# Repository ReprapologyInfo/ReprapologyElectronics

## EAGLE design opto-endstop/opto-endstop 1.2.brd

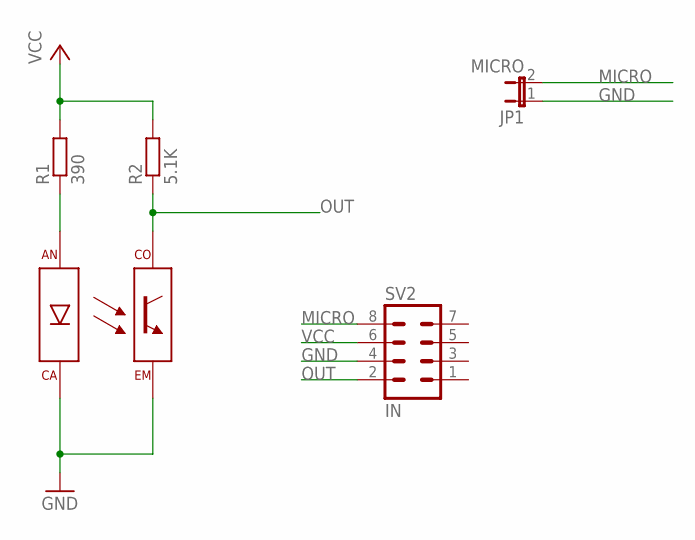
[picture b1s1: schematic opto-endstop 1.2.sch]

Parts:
JP1: MICRO; JP1
R1: 390; 0204/5
R2: 5.1K; 0204/5
SV2: IN; MA04-2
U$1: KTIR0521DS

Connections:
GND: JP1.1, SV2.4, U$1.CA, U$1.EM
MICRO: JP1.2, SV2.8
unnamed: R1.1, U$1.AN
OUT: R2.1, SV2.2, U$1.CO
VCC: R1.2, R2.2, SV2.6

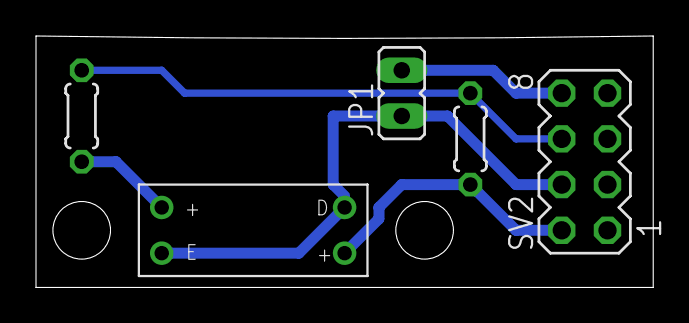
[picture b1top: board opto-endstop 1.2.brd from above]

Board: 2 copper layers, 34.3 x 14.0 mm, 5 parts (0 on the bottom side), 5 nets.

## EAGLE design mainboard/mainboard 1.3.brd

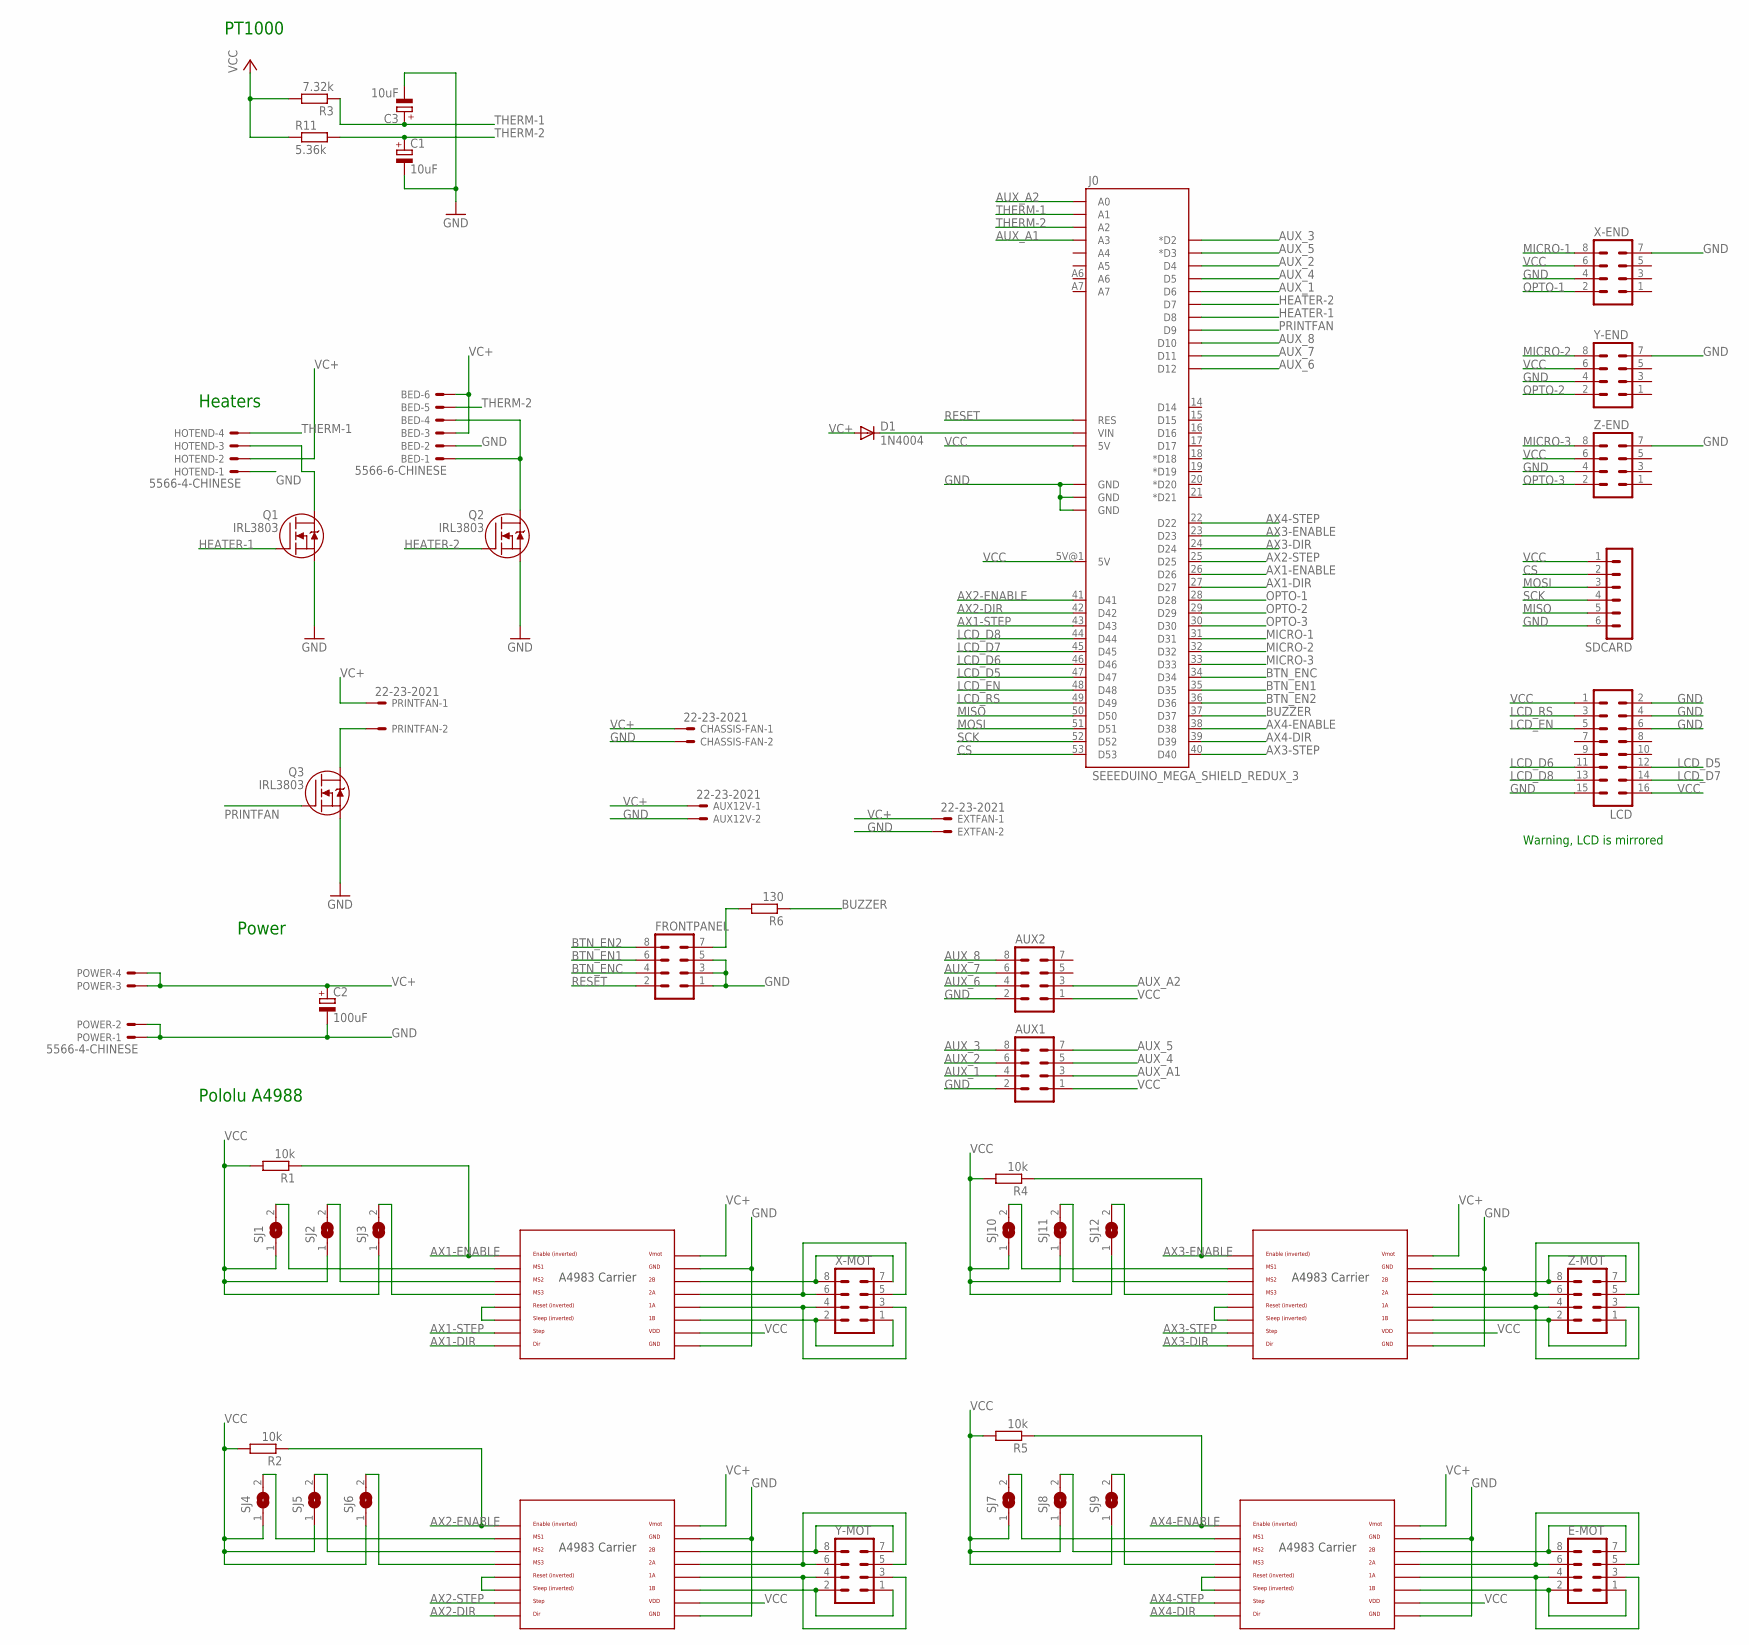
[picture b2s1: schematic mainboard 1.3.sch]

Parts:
AUX1: MA04-2-HOLES; MA04-2
AUX2: MA04-2; MA04-2@1
AUX12V: 22-23-2021; MPN 22-23-2021
BED: 5566-6-CHINESE
C1, C3: 10uF; E2,5-6
C2: 100uF; E2,5-6
CHASSIS-FAN: 22-23-2021; MPN 22-23-2021
D1: 1N4004; DO41-10
E-AXIS: POLOLU_A4983CARRIER; A4983CARRIER
E-MOT: MA04-2; MA04-2@1
EXTFAN: 22-23-2021; MPN 22-23-2021
FRONTPANEL: MA04-2; MA04-2@1
HOTEND: 5566-4-CHINESE
J0: SEEEDUINO_MEGA_SHIELD_REDUX_3
LCD: MA08-2
POWER: 5566-4-CHINESE
PRINTFAN: 22-23-2021
Q1, Q2, Q3: IRL3803; TO220AB
R1, R2, R4, R5: 10k; 0204/7
R3: 7.32k; 0204/7
R6: 130; 0204/7
R11: 5.36k; 0204/7
SDCARD: MA06-1
SJ1, SJ2, SJ3, SJ4, SJ5, SJ6, SJ7, SJ8, SJ9, SJ10, SJ11, SJ12: SJ
X-AXIS: POLOLU_A4983CARRIER; A4983CARRIER
X-END: MA04-2; MA04-2@1
X-MOT: MA04-2; MA04-2@1
Y-AXIS: POLOLU_A4983CARRIER; A4983CARRIER
Y-END: MA04-2; MA04-2@1
Y-MOT: MA04-2; MA04-2@1
Z-AXIS: POLOLU_A4983CARRIER; A4983CARRIER
Z-END: MA04-2; MA04-2@1
Z-MOT: MA04-2; MA04-2@1

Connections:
AUX_1: AUX1.4, J0.6 (D6)
AUX_2: AUX1.6, J0.4 (D4)
AUX_3: AUX1.8, J0.2 (*D2)
AUX_4: AUX1.5, J0.5 (D5)
AUX_5: AUX1.7, J0.3 (*D3)
AUX_6: AUX2.4, J0.12 (D12)
AUX_7: AUX2.6, J0.11 (D11)
AUX_8: AUX2.8, J0.10 (D10)
AUX_A1: AUX1.3, J0.A3
AUX_A2: AUX2.3, J0.A0
AX1-DIR: J0.27 (D27), X-AXIS.DIR
AX1-ENABLE: J0.26 (D26), R1.1, X-AXIS.EN
AX1-STEP: J0.43 (D43), X-AXIS.STEP
AX2-DIR: J0.42 (D42), Y-AXIS.DIR
AX2-ENABLE: J0.41 (D41), R2.1, Y-AXIS.EN
AX2-STEP: J0.25 (D25), Y-AXIS.STEP
AX3-DIR: J0.24 (D24), Z-AXIS.DIR
AX3-ENABLE: J0.23 (D23), R4.1, Z-AXIS.EN
AX3-STEP: J0.40 (D40), Z-AXIS.STEP
AX4-DIR: E-AXIS.DIR, J0.39 (D39)
AX4-ENABLE: E-AXIS.EN, J0.38 (D38), R5.1
AX4-STEP: E-AXIS.STEP, J0.22 (D22)
BTN_EN1: FRONTPANEL.6, J0.35 (D35)
BTN_EN2: FRONTPANEL.8, J0.36 (D36)
BTN_ENC: FRONTPANEL.4, J0.34 (D34)
BUZZER: J0.37 (D37), R6.1
CS: J0.53 (D53), SDCARD.2
GND: AUX1.2, AUX2.2, AUX12V.2, BED.2, C1.-, C2.-, C3.-, CHASSIS-FAN.2, E-AXIS.GND, E-AXIS.GND@0 (GND), EXTFAN.2, FRONTPANEL.1, FRONTPANEL.3, FRONTPANEL.5, HOTEND.1, J0.GND@0 (GND), J0.GND@1 (GND), J0.GND@2 (GND), LCD.2, LCD.4, LCD.6, LCD.15, POWER.1, POWER.2, Q1.S, Q2.S, Q3.S, SDCARD.6, X-AXIS.GND, X-AXIS.GND@0 (GND), X-END.4, X-END.7, Y-AXIS.GND, Y-AXIS.GND@0 (GND), Y-END.4, Y-END.7, Z-AXIS.GND, Z-AXIS.GND@0 (GND), Z-END.4, Z-END.7
HEATER-1: J0.8 (D8), Q1.G
HEATER-2: J0.7 (D7), Q2.G
LCD_D5: J0.47 (D47), LCD.12
LCD_D6: J0.46 (D46), LCD.11
LCD_D7: J0.45 (D45), LCD.14
LCD_D8: J0.44 (D44), LCD.13
LCD_EN: J0.48 (D48), LCD.5
LCD_RS: J0.49 (D49), LCD.3
MICRO-1: J0.31 (D31), X-END.8
MICRO-2: J0.32 (D32), Y-END.8
MICRO-3: J0.33 (D33), Z-END.8
MISO: J0.50 (D50), SDCARD.5
MOSI: J0.51 (D51), SDCARD.3
unnamed: BED.1, BED.4, Q2.D
unnamed: FRONTPANEL.7, R6.2
unnamed: X-AXIS.RST, X-AXIS.SLP (SLEEP)
unnamed: SJ3.2, X-AXIS.MS3
unnamed: SJ2.2, X-AXIS.MS2
unnamed: SJ1.2, X-AXIS.MS1
unnamed: X-AXIS.2B, X-MOT.7, X-MOT.8
unnamed: X-AXIS.2A, X-MOT.5, X-MOT.6
unnamed: X-AXIS.1A, X-MOT.3, X-MOT.4
unnamed: X-AXIS.1B, X-MOT.1, X-MOT.2
unnamed: PRINTFAN.2, Q3.D
unnamed: Z-AXIS.RST, Z-AXIS.SLP (SLEEP)
unnamed: D1.C, J0.VIN
unnamed: SJ12.2, Z-AXIS.MS3
unnamed: SJ11.2, Z-AXIS.MS2
unnamed: SJ10.2, Z-AXIS.MS1
unnamed: Z-AXIS.2B, Z-MOT.7, Z-MOT.8
unnamed: Z-AXIS.2A, Z-MOT.5, Z-MOT.6
unnamed: Z-AXIS.1A, Z-MOT.3, Z-MOT.4
unnamed: Z-AXIS.1B, Z-MOT.1, Z-MOT.2
unnamed: Y-AXIS.RST, Y-AXIS.SLP (SLEEP)
unnamed: SJ6.2, Y-AXIS.MS3
unnamed: SJ5.2, Y-AXIS.MS2
unnamed: SJ4.2, Y-AXIS.MS1
unnamed: Y-AXIS.2B, Y-MOT.7, Y-MOT.8
unnamed: Y-AXIS.2A, Y-MOT.5, Y-MOT.6
unnamed: Y-AXIS.1A, Y-MOT.3, Y-MOT.4
unnamed: Y-AXIS.1B, Y-MOT.1, Y-MOT.2
unnamed: E-AXIS.RST, E-AXIS.SLP (SLEEP)
unnamed: E-AXIS.MS3, SJ9.2
unnamed: E-AXIS.MS2, SJ8.2
unnamed: E-AXIS.MS1, SJ7.2
unnamed: E-AXIS.2B, E-MOT.7, E-MOT.8
unnamed: E-AXIS.2A, E-MOT.5, E-MOT.6
unnamed: E-AXIS.1A, E-MOT.3, E-MOT.4
unnamed: E-AXIS.1B, E-MOT.1, E-MOT.2
unnamed: HOTEND.3, Q1.D
OPTO-1: J0.28 (D28), X-END.2
OPTO-2: J0.29 (D29), Y-END.2
OPTO-3: J0.30 (D30), Z-END.2
PRINTFAN: J0.9 (D9), Q3.G
RESET: FRONTPANEL.2, J0.RST (RES)
SCK: J0.52 (D52), SDCARD.4
THERM-1: C3.+, HOTEND.4, J0.A1, R3.1
THERM-2: BED.5, C1.+, J0.A2, R11.2
VC+: AUX12V.1, BED.3, BED.6, C2.+, CHASSIS-FAN.1, D1.A, E-AXIS.VMOT, EXTFAN.1, HOTEND.2, POWER.3, POWER.4, PRINTFAN.1, X-AXIS.VMOT, Y-AXIS.VMOT, Z-AXIS.VMOT
VCC: AUX1.1, AUX2.1, E-AXIS.VDD, J0.5V@0 (5V), J0.5V@1 (5V), LCD.1, LCD.16, R1.2, R2.2, R3.2, R4.2, R5.2, R11.1, SDCARD.1, SJ1.1, SJ2.1, SJ3.1, SJ4.1, SJ5.1, SJ6.1, SJ7.1, SJ8.1, SJ9.1, SJ10.1, SJ11.1, SJ12.1, X-AXIS.VDD, X-END.6, Y-AXIS.VDD, Y-END.6, Z-AXIS.VDD, Z-END.6

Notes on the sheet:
Power
Heaters
PT1000
Pololu A4988
Warning, LCD is mirrored

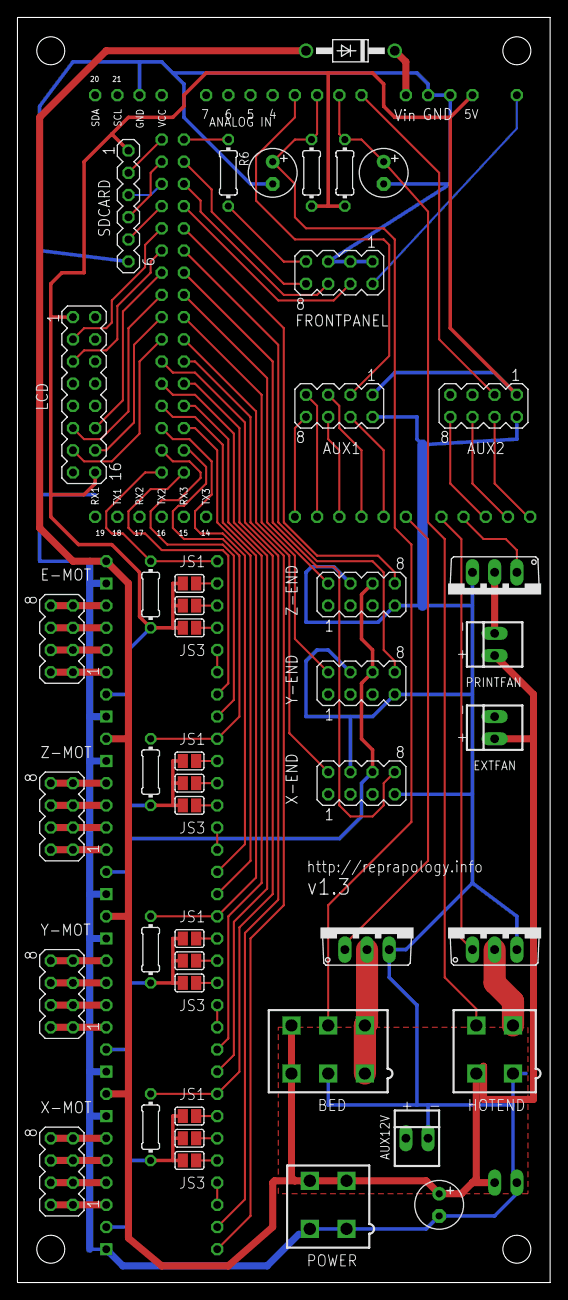
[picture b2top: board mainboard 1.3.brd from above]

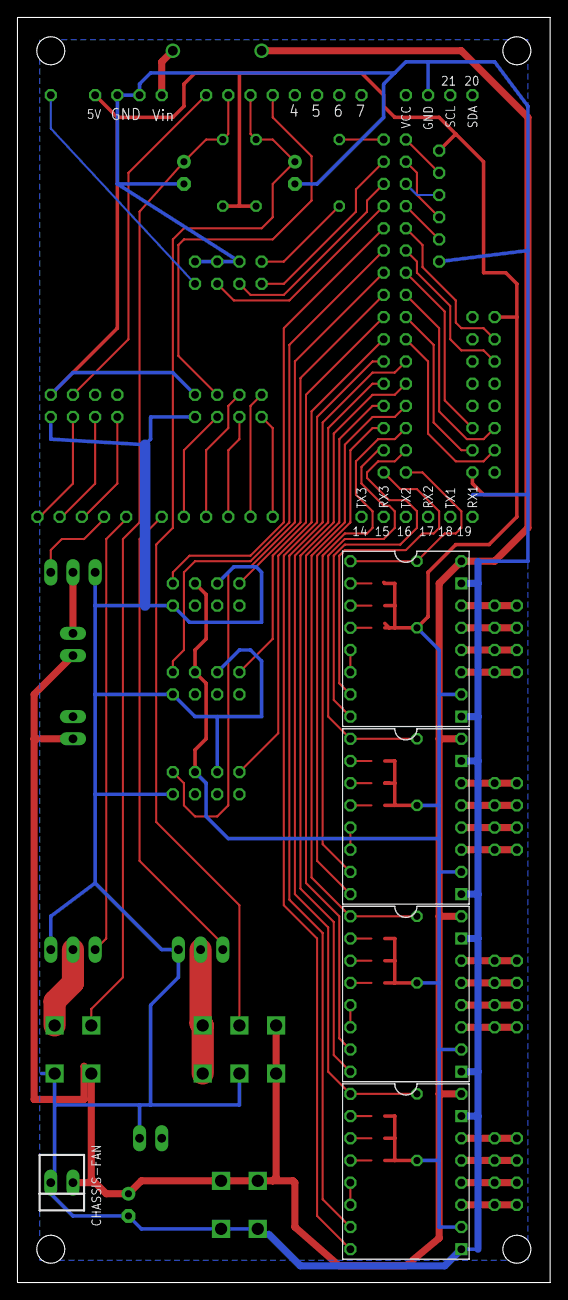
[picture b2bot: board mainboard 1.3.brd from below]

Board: 2 copper layers, 61.0 x 144.8 mm, 50 parts (5 on the bottom side), 88 nets.

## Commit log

2013-06-29 Initial commit
    Reprapology v1.3 electronics. No longer quite so universal as Urd
    series, so I suppose it merits a new repository.
